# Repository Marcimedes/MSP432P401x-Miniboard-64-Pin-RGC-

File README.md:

# MSP432P401x-Miniboard-64-Pin-RGC

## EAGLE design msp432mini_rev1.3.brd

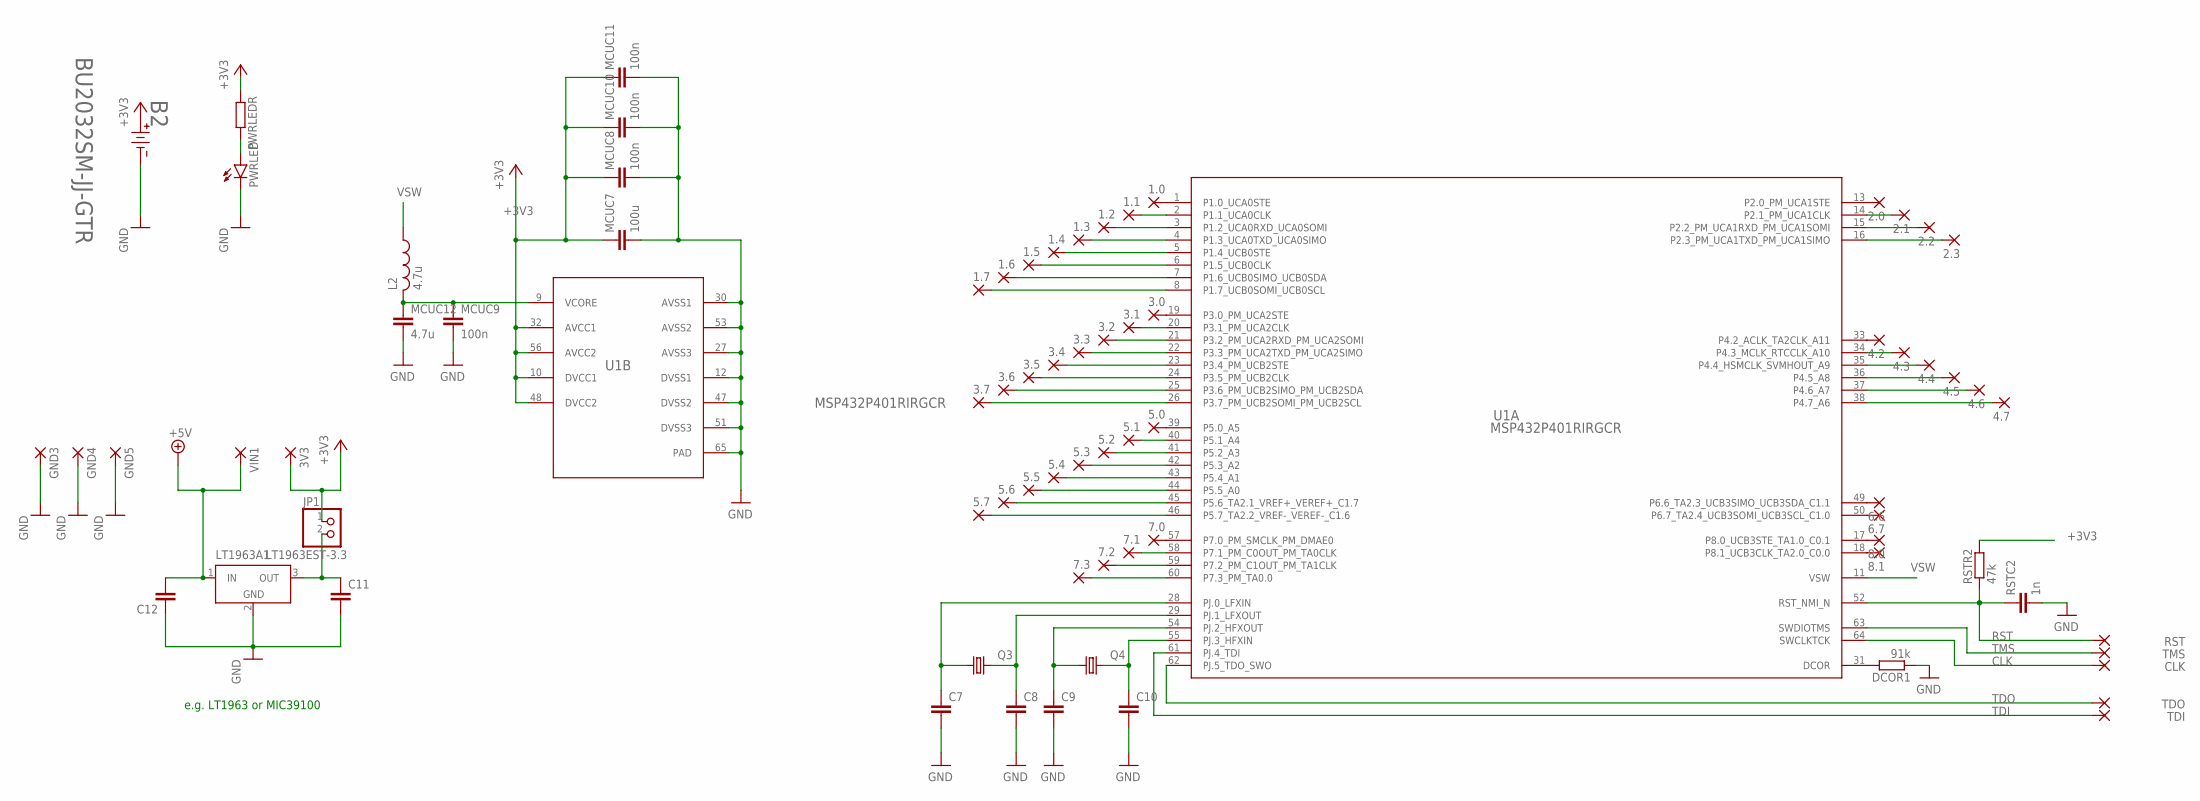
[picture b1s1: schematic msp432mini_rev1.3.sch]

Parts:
1.0, 1.1, 1.2, 1.3, 1.4, 1.5, 1.6, 1.7, 2.0, 2.1, 2.2, 2.3, 3.0, 3.1, 3.2, 3.3, 3.4, 3.5, 3.6, 3.7, 3V3, 4.2, 4.3, 4.4, 4.5, 4.6, 4.7, 5.0, 5.1, 5.2, 5.3, 5.4, 5.5, 5.6, 5.7, 6.6, 6.7, 7.0, 7.1, 7.2, 7.3, 8.0, 8.1: 1,6/0,9
B2: BU2032SM-JJ-GTR; BU2032SM-JJ-GTR_MPD
C7, C8, C9, C10: C-EUC0402K; C0402K
C11, C12: C-EUC1206K; C1206K
CLK: 1,6/0,9
DCOR1: 91k; R0603
GND3, GND4, GND5: 1,6/0,9
JP1: PINHD-1X2; 1X02
L2: 4.7u; L2012C
LT1963A1: LT1963EST-3.3; SOT223
MCUC7: 100u; C1206K
MCUC8, MCUC9, MCUC10, MCUC11: 100n; C0603K
MCUC12: 4.7u; C0603K
PWRLED: LEDCHIP-LED0805; CHIP-LED0805
PWRLEDR: R-EU_R0603; R0603
Q3: KX-327-NHF; 3.2X1.5
Q4: KX-7; 3.2X2.5_KX-7
RST: 1,6/0,9
RSTC2: 1n; C0603K
RSTR2: 47k; R0603
TDI: 1,6/0,9
TDO: 1,6/0,9
TMS: 1,6/0,9
U1: MSP432P401RIRGCR; RGC0064B
VIN1: 1,6/0,9

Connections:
+3V3: 3V3.1, B2.2, JP1.1, MCUC7.1, MCUC8.1, MCUC10.1, MCUC11.1, PWRLEDR.1, RSTR2.2, U1.10 (DVCC1), U1.32 (AVCC1), U1.48 (DVCC2), U1.56 (AVCC2)
+5V: C12.2, LT1963A1.1 (IN), VIN1.1
CLK: CLK.1, U1.64 (SWCLKTCK)
GND: B2.1, C7.2, C8.2, C9.2, C10.2, C11.2, C12.1, DCOR1.1, GND3.1, GND4.1, GND5.1, LT1963A1.2 (GND), LT1963A1.4 (GND), MCUC7.2, MCUC8.2, MCUC9.2, MCUC10.2, MCUC11.2, MCUC12.2, PWRLED.C, RSTC2.2, U1.12 (DVSS1), U1.27 (AVSS3), U1.30 (AVSS1), U1.47 (DVSS2), U1.51 (DVSS3), U1.53 (AVSS2), U1.65 (PAD)
unnamed: C11.1, JP1.2, LT1963A1.3 (OUT)
unnamed: L2.2, MCUC9.1, MCUC12.1, U1.9 (VCORE)
unnamed: C7.1, Q3.1, U1.28 (PJ.0_LFXIN)
unnamed: C8.1, Q3.2, U1.29 (PJ.1_LFXOUT)
unnamed: 5.0.1, U1.39 (P5.0_A5)
unnamed: 4.2.1, U1.33 (P4.2_ACLK_TA2CLK_A11)
unnamed: PWRLED.A, PWRLEDR.2
unnamed: C10.1, Q4.3 (2), U1.55 (PJ.3_HFXIN)
unnamed: C9.1, Q4.1, U1.54 (PJ.2_HFXOUT)
unnamed: 3.0.1, U1.19 (P3.0_PM_UCA2STE)
unnamed: 3.1.1, U1.20 (P3.1_PM_UCA2CLK)
unnamed: 3.2.1, U1.21 (P3.2_PM_UCA2RXD_PM_UCA2SOMI)
unnamed: 3.3.1, U1.22 (P3.3_PM_UCA2TXD_PM_UCA2SIMO)
unnamed: 3.4.1, U1.23 (P3.4_PM_UCB2STE)
unnamed: 3.5.1, U1.24 (P3.5_PM_UCB2CLK)
unnamed: 3.6.1, U1.25 (P3.6_PM_UCB2SIMO_PM_UCB2SDA)
unnamed: 3.7.1, U1.26 (P3.7_PM_UCB2SOMI_PM_UCB2SCL)
unnamed: 5.1.1, U1.40 (P5.1_A4)
unnamed: 5.2.1, U1.41 (P5.2_A3)
unnamed: 5.3.1, U1.42 (P5.3_A2)
unnamed: 5.4.1, U1.43 (P5.4_A1)
unnamed: 5.5.1, U1.44 (P5.5_A0)
unnamed: 5.6.1, U1.45 (P5.6_TA2.1_VREF+_VEREF+_C1.7)
unnamed: 5.7.1, U1.46 (P5.7_TA2.2_VREF-_VEREF-_C1.6)
unnamed: 4.3.1, U1.34 (P4.3_MCLK_RTCCLK_A10)
unnamed: 4.4.1, U1.35 (P4.4_HSMCLK_SVMHOUT_A9)
unnamed: 4.5.1, U1.36 (P4.5_A8)
unnamed: 4.6.1, U1.37 (P4.6_A7)
unnamed: 4.7.1, U1.38 (P4.7_A6)
unnamed: 2.0.1, U1.13 (P2.0_PM_UCA1STE)
unnamed: 2.1.1, U1.14 (P2.1_PM_UCA1CLK)
unnamed: 2.2.1, U1.15 (P2.2_PM_UCA1RXD_PM_UCA1SOMI)
unnamed: 2.3.1, U1.16 (P2.3_PM_UCA1TXD_PM_UCA1SIMO)
unnamed: 1.0.1, U1.1 (P1.0_UCA0STE)
unnamed: 1.1.1, U1.2 (P1.1_UCA0CLK)
unnamed: 1.2.1, U1.3 (P1.2_UCA0RXD_UCA0SOMI)
unnamed: 1.3.1, U1.4 (P1.3_UCA0TXD_UCA0SIMO)
unnamed: 1.4.1, U1.5 (P1.4_UCB0STE)
unnamed: 1.5.1, U1.6 (P1.5_UCB0CLK)
unnamed: 1.6.1, U1.7 (P1.6_UCB0SIMO_UCB0SDA)
unnamed: 1.7.1, U1.8 (P1.7_UCB0SOMI_UCB0SCL)
unnamed: 6.6.1, U1.49 (P6.6_TA2.3_UCB3SIMO_UCB3SDA_C1.1)
unnamed: 6.7.1, U1.50 (P6.7_TA2.4_UCB3SOMI_UCB3SCL_C1.0)
unnamed: 8.0.1, U1.17 (P8.0_UCB3STE_TA1.0_C0.1)
unnamed: 8.1.1, U1.18 (P8.1_UCB3CLK_TA2.0_C0.0)
unnamed: 7.0.1, U1.57 (P7.0_PM_SMCLK_PM_DMAE0)
unnamed: 7.1.1, U1.58 (P7.1_PM_C0OUT_PM_TA0CLK)
unnamed: 7.2.1, U1.59 (P7.2_PM_C1OUT_PM_TA1CLK)
unnamed: 7.3.1, U1.60 (P7.3_PM_TA0.0)
unnamed: DCOR1.2, U1.31 (DCOR)
RST: RST.1, RSTC2.1, RSTR2.1, U1.52 (RST_NMI_N)
TDI: TDI.1, U1.61 (PJ.4_TDI)
TDO: TDO.1, U1.62 (PJ.5_TDO_SWO)
TMS: TMS.1, U1.63 (SWDIOTMS)
VSW: L2.1, U1.11 (VSW)

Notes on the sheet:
e.g. LT1963 or MIC39100

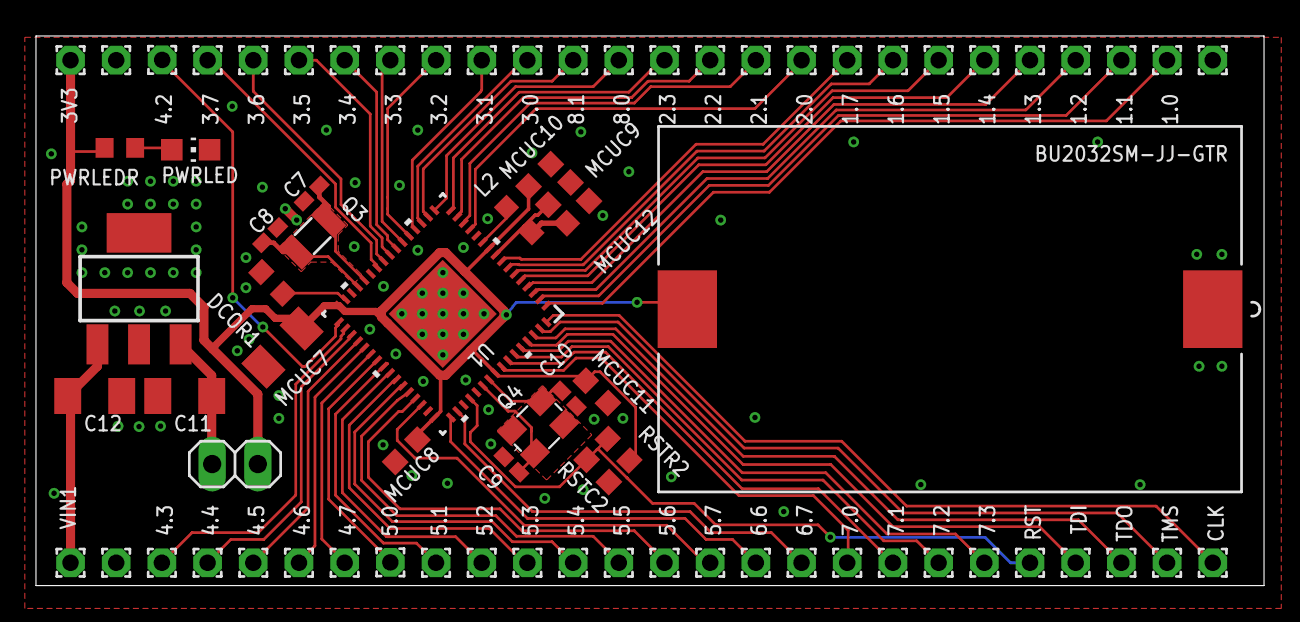
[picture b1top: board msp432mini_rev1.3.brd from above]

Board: 2 copper layers, 68.3 x 30.6 mm, 76 parts (0 on the bottom side), 59 nets.

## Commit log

2021-07-09 gerber

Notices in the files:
parts and their libraries:
crystal-geyer_V1_0: Copyright: Geyer-Electronic
COPYRIGHT: Copyright (C) 2018 Accelerated Designs. All rights reserved
